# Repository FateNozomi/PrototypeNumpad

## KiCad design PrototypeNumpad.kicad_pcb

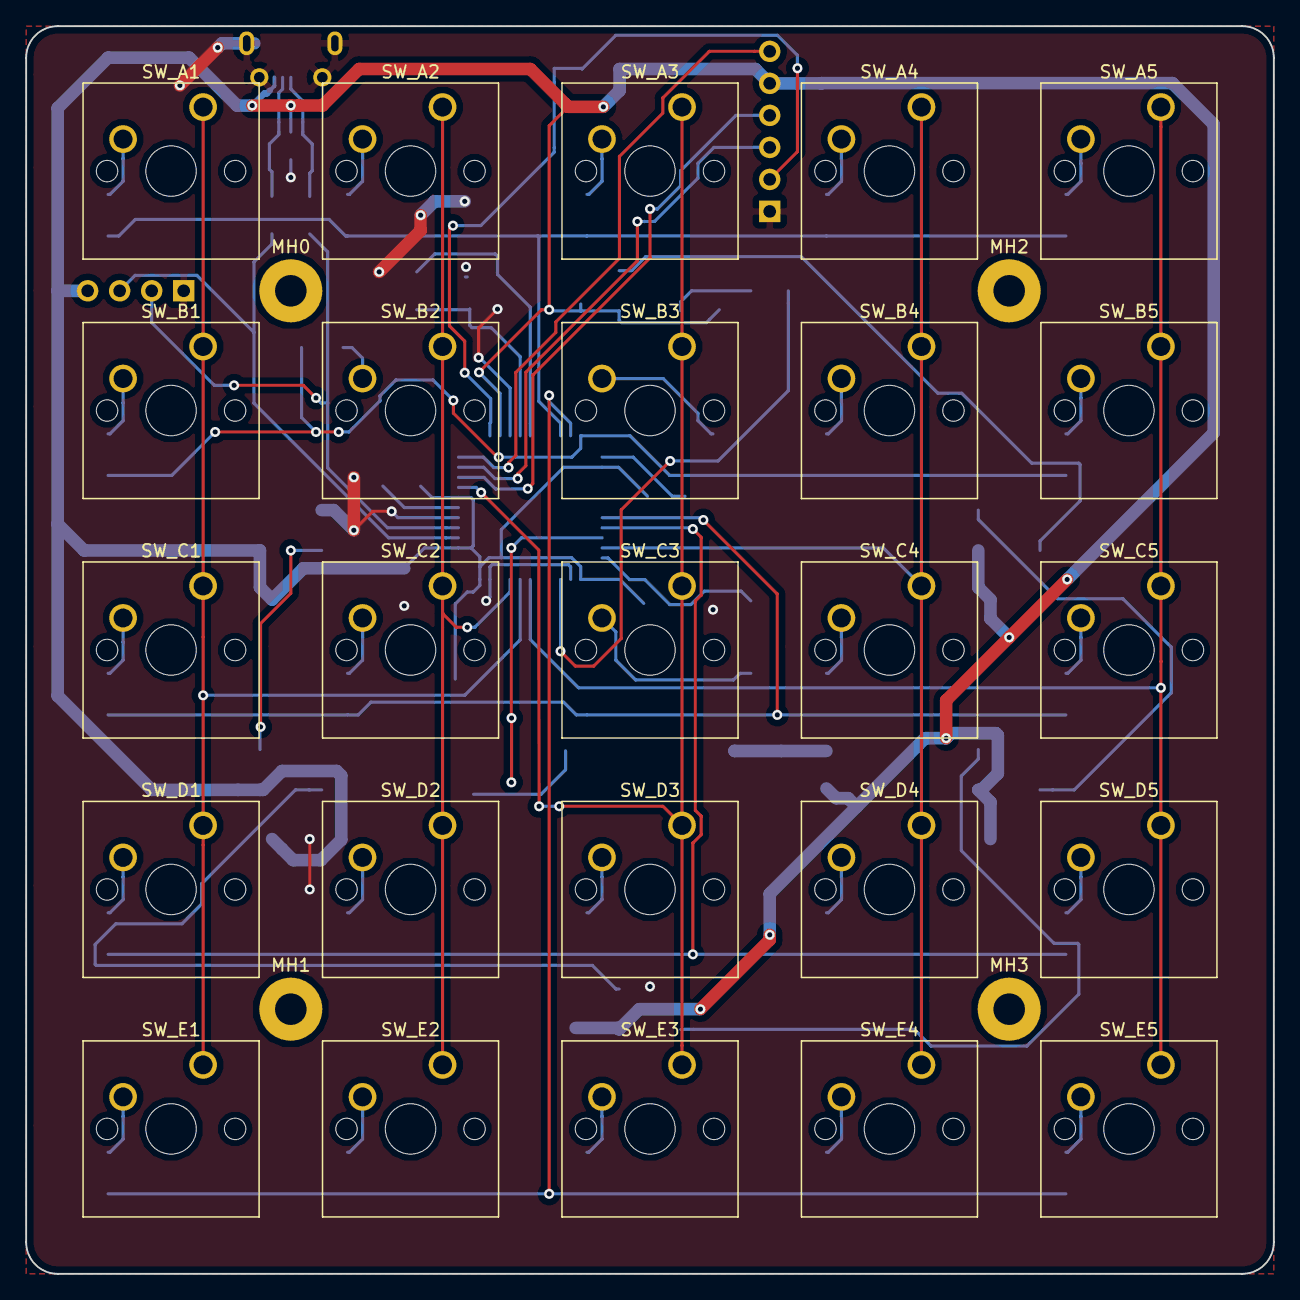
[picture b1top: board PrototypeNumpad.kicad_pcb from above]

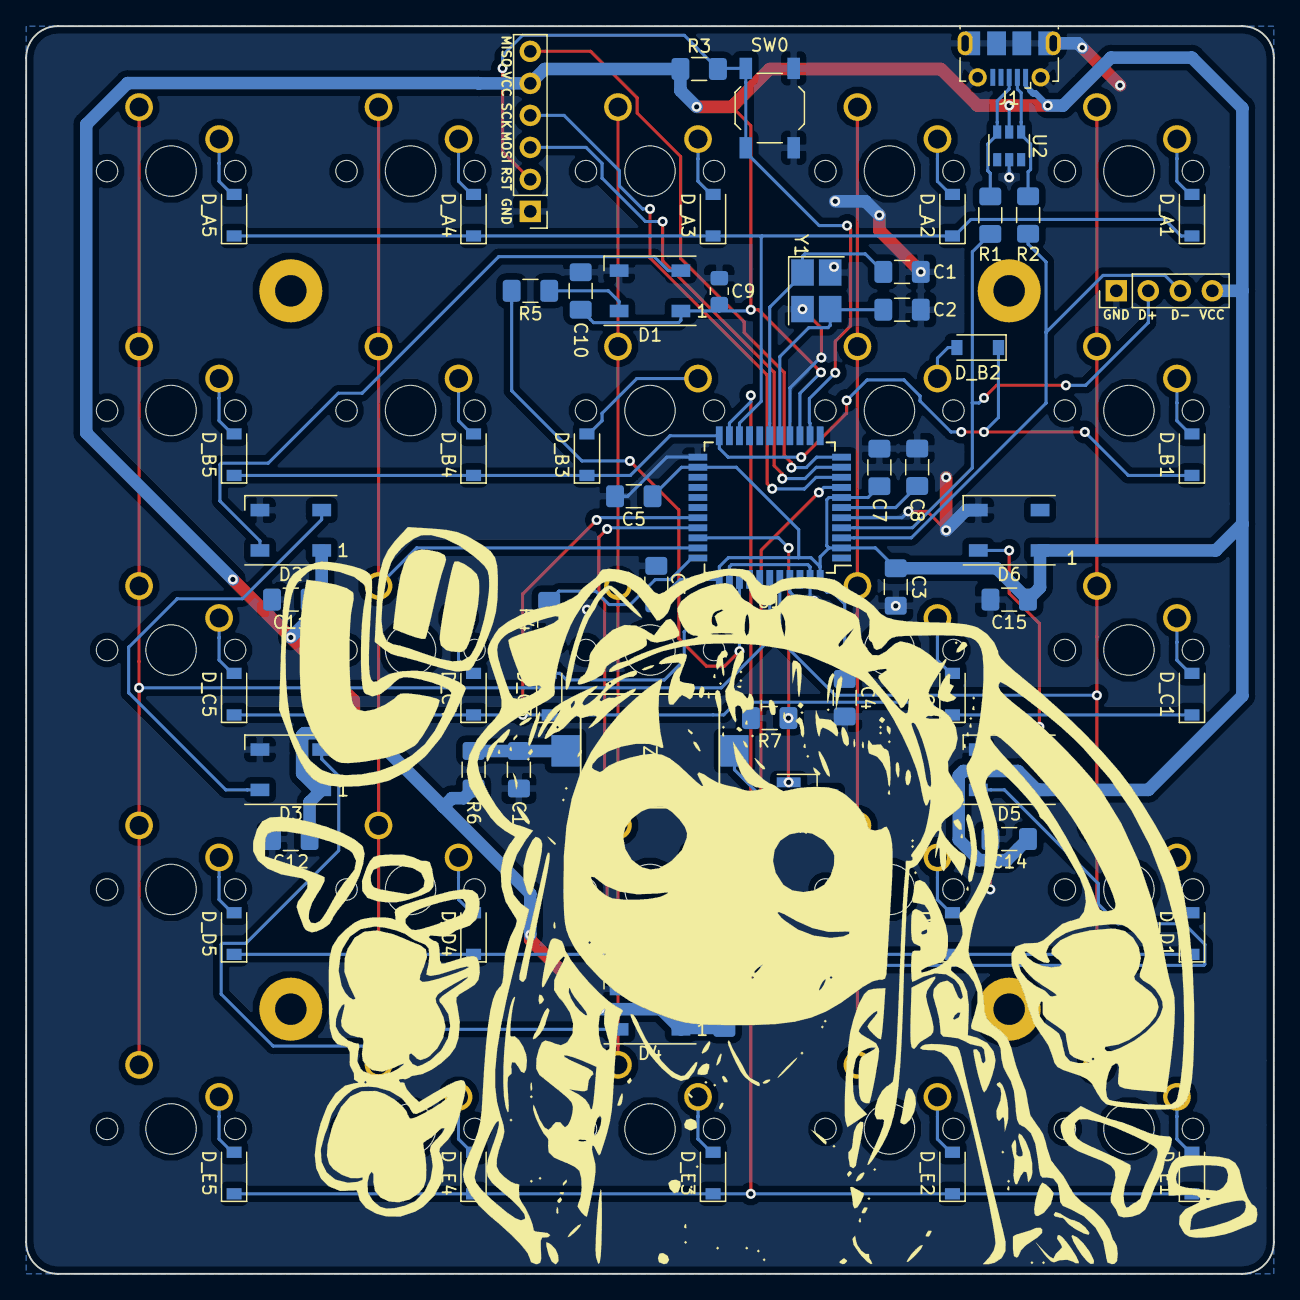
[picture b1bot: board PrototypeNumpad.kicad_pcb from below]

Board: 2 copper layers, 99.0 x 99.0 mm, 92 parts (63 on the bottom side), 59 nets.

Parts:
BZ1: Buzzer; Buzzer_AST1109MLTRQ
C1, C2: 22pF; C_1206_3216Metric_Pad1.42x1.75mm_HandSolder
C3, C10, C11, C12, C13, C14, C15: 0.1uF; C_1206_3216Metric_Pad1.42x1.75mm_HandSolder
C4: 1F; C_1206_3216Metric_Pad1.42x1.75mm_HandSolder
C5, C8: 1uF; C_1206_3216Metric_Pad1.42x1.75mm_HandSolder
C6, C7, C16: 10uF; C_1206_3216Metric_Pad1.42x1.75mm_HandSolder
C9: 47uF; C_0805_2012Metric_Pad1.15x1.40mm_HandSolder
D1, D2, D3, D4, D5, D6: WS2812B; LED_WS2812B_PLCC4_5.0x5.0mm_P3.2mm
D_A1, D_A2, D_A3, D_A4, D_A5: D; D_SOD-123
D_B1, D_B2, D_B3, D_B4, D_B5: D; D_SOD-123
D_C1, D_C2, D_C3, D_C4, D_C5: D; D_SOD-123
D_D1, D_D2, D_D3, D_D4, D_D5: D; D_SOD-123
D_E1, D_E2, D_E3, D_E4, D_E5: D; D_SOD-123
J0: Conn_01x06; PinHeader_1x06_P2.54mm_Vertical
J1: USB_B_Micro; USB_Micro-B_Molex-105017-0001
J1A1: Conn_01x04; PinHeader_1x04_P2.54mm_Vertical
MH0, MH1, MH2, MH3: MountingHole; MountingHole_2.5mm_Pad
Q1: 2N7002; SOT-23_Handsoldering
R1, R2: 22; R_1206_3216Metric_Pad1.42x1.75mm_HandSolder
R3, R4, R7: 10K; R_1206_3216Metric_Pad1.42x1.75mm_HandSolder
R5, R6: 470; R_1206_3216Metric_Pad1.42x1.75mm_HandSolder
SW0: SW_Push; SW_SPST_TL3342
SW_A1, SW_A2, SW_A3, SW_A4, SW_A5: SW_Push; SW_Cherry_MX1A_1.00u_PCB
SW_B1, SW_B2, SW_B3, SW_B4, SW_B5: SW_Push; SW_Cherry_MX1A_1.00u_PCB
SW_C1, SW_C2, SW_C3, SW_C4, SW_C5: SW_Push; SW_Cherry_MX1A_1.00u_PCB
SW_D1, SW_D2, SW_D3, SW_D4, SW_D5: SW_Push; SW_Cherry_MX1A_1.00u_PCB
SW_E1, SW_E2, SW_E3, SW_E4, SW_E5: SW_Push; SW_Cherry_MX1A_1.00u_PCB
U1: ATmega32U4-AU; TQFP-44_10x10mm_P0.8mm
U2: USBLC6-2SC6; SOT-23-6
Y1: Crystal_GND24; Crystal_SMD_SeikoEpson_FA238-4Pin_3.2x2.5mm_HandSoldering

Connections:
Col1: SW_A1.1, SW_B1.1, SW_C1.1, SW_D1.1, SW_E1.1, U1.40
Col2: SW_A2.1, SW_B2.1, SW_C2.1, SW_D2.1, SW_E2.1, U1.41
Col3: SW_A3.1, SW_B3.1, SW_C3.1, SW_D3.1, SW_E3.1, U1.8
Col4: SW_A4.1, SW_B4.1, SW_C4.1, SW_D4.1, SW_E4.1, U1.32
Col5: SW_A5.1, SW_B5.1, SW_C5.1, SW_D5.1, SW_E5.1, U1.39
D+: J1A1.2, R1.1, U1.4
D-: J1A1.3, R2.1, U1.3
GND: C1.1, C2.2, C3.2, C4.2, C5.2, C6.2, C7.2, C8.2, C9.2, C10.2, C11.2, C12.2, C13.2, C14.2, C15.2, C16.2, D1.3, D2.3, D3.3, D4.3, D5.3, D6.3, J0.1, J1.5, J1.6, J1A1.1, Q1.2, R4.1, R7.2, SW0.1, U1.5, U1.15, U1.23, U1.35, U1.43, U2.2, Y1.2, Y1.4
MISO: J0.6, U1.11
MOSI: J0.3, U1.10
unnamed: BZ1.1, C16.1, R6.1
unnamed: BZ1.2, Q1.3
unnamed: C8.1, U1.6
unnamed: D1.2, D2.4
unnamed: D1.4, R5.1
unnamed: D2.2, D3.4
unnamed: D3.2, D4.4
unnamed: D4.2, D5.4
unnamed: D5.2, D6.4
unnamed: D_A1.2, SW_A1.2
unnamed: D_A2.2, SW_A2.2
unnamed: D_A3.2, SW_A3.2
unnamed: D_A4.2, SW_A4.2
unnamed: D_A5.2, SW_A5.2
unnamed: D_B1.2, SW_B1.2
unnamed: D_B2.2, SW_B2.2
unnamed: D_B3.2, SW_B3.2
unnamed: D_B4.2, SW_B4.2
unnamed: D_B5.2, SW_B5.2
unnamed: D_C1.2, SW_C1.2
unnamed: D_C2.2, SW_C2.2
unnamed: D_C3.2, SW_C3.2
unnamed: D_C4.2, SW_C4.2
unnamed: D_C5.2, SW_C5.2
unnamed: D_D1.2, SW_D1.2
unnamed: D_D2.2, SW_D2.2
unnamed: D_D3.2, SW_D3.2
unnamed: D_D4.2, SW_D4.2
unnamed: D_D5.2, SW_D5.2
unnamed: D_E1.2, SW_E1.2
unnamed: D_E2.2, SW_E2.2
unnamed: D_E3.2, SW_E3.2
unnamed: D_E4.2, SW_E4.2
unnamed: D_E5.2, SW_E5.2
unnamed: J1.2, R2.2, U2.4
unnamed: J1.3, R1.2, U2.6
unnamed: R4.2, U1.33
RGB: R5.2, U1.36
RST: J0.2, R3.2, SW0.2, U1.13
RowA: D_A1.1, D_A2.1, D_A3.1, D_A4.1, D_A5.1, U1.20
RowB: D_B1.1, D_B2.1, D_B3.1, D_B4.1, D_B5.1, U1.22
RowC: D_C1.1, D_C2.1, D_C3.1, D_C4.1, D_C5.1, U1.29
RowD: D_D1.1, D_D2.1, D_D3.1, D_D4.1, D_D5.1, U1.30
RowE: D_E1.1, D_E2.1, D_E3.1, D_E4.1, D_E5.1, U1.21
SCK: J0.4, U1.9
SPEAKER: Q1.1, R7.1, U1.31
VCC: C3.1, C4.1, C5.1, C6.1, C7.1, C9.1, C10.1, C11.1, C12.1, C13.1, C14.1, C15.1, D1.1, D2.1, D3.1, D4.1, D5.1, D6.1, J0.5, J1.1, J1A1.4, R3.1, R6.2, U1.2, U1.7, U1.14, U1.24, U1.34, U1.44, U2.5
XTAL1: C1.2, U1.17, Y1.1
XTAL2: C2.1, U1.16, Y1.3

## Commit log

2018-10-09 Add ISP connectors
2018-10-10 Add RGB underglow
2018-10-10 Add switch A1
2018-10-10 Assign PCB footprints to schematic symbols
2018-10-11 Change Crystal grounding pins
2018-10-11 Add M2.5 mounting holes
2018-10-12 Arrange all components on PCB
2018-10-12 Route tracks
2018-10-12 Re position References
2018-10-12 Expose USB traces as headers
2018-10-12 Add Header References
2018-10-12 Re-position capacitor C9
2018-10-16 Add Speaker
2018-10-16 Add speaker to PCB
2018-10-16 Organize pin headers
2018-10-19 Add Gerber
2018-11-02 Add Komi-san to Silkscreen layer
2018-12-07 Update ATmega32u4 decoupling capacitor values
2018-12-07 Export Eeschema to pdf
2018-12-07 Generate Bill of Materials as csv file
